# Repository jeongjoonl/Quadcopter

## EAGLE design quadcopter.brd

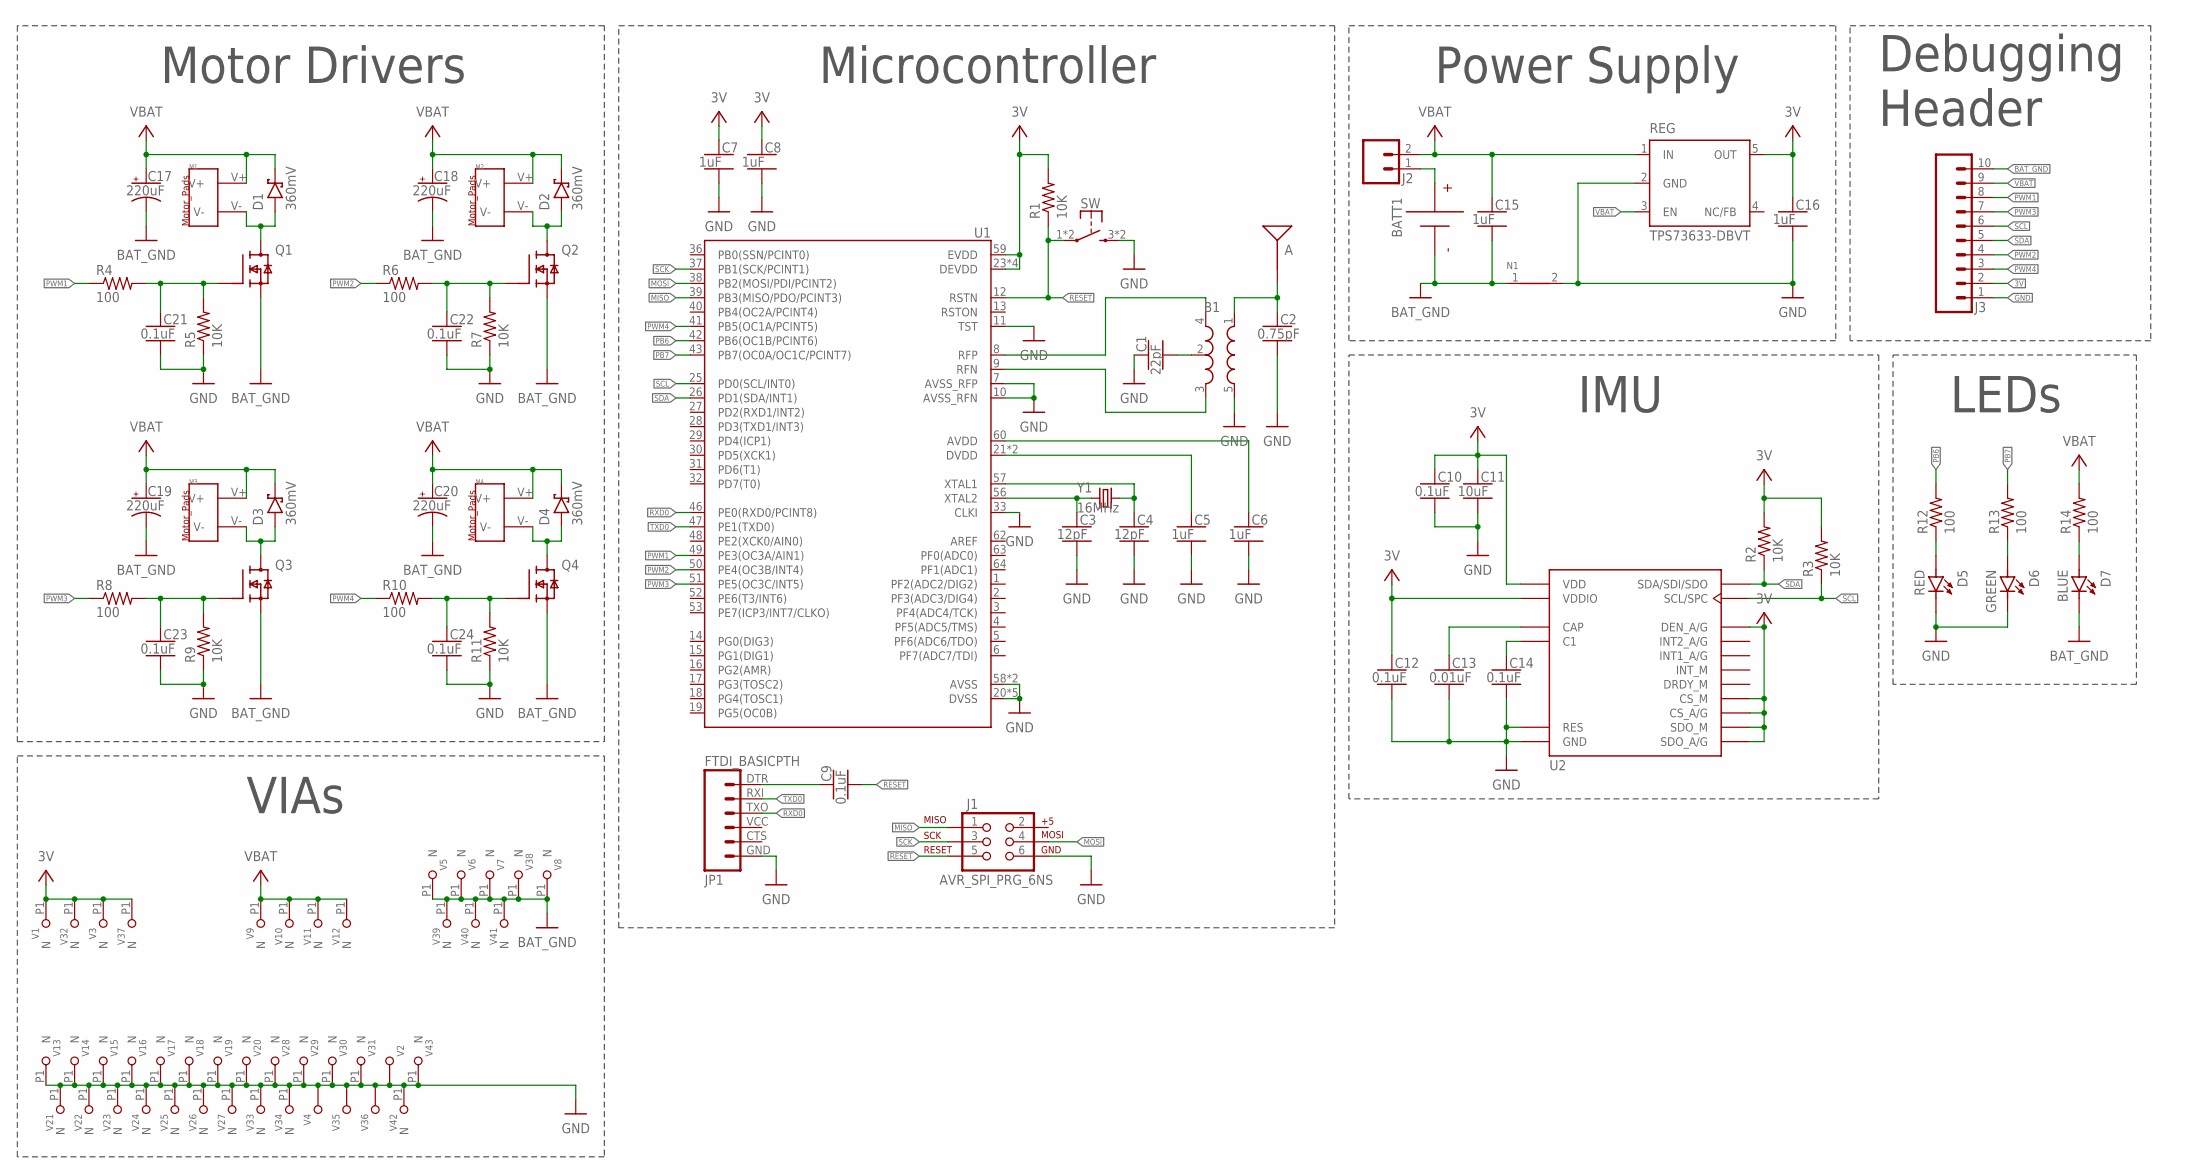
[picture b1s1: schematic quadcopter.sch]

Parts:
A: ANTENNA2SMD5; ANTENNA-CHIP5
B1: BALUN0805; BALUN
BATT1: BATTERY; BATTERY-TERMINALS
C1: 22pF; CAPC2012X140_HS
C2: 0.75pF; CAPC2012X140_HS
C3, C4: 12pF; CAPC2012X140_HS
C5, C6, C7, C8, C15, C16: 1uF; CAPC2012X140_HS
C9, C10, C12, C14, C21, C22, C23, C24: 0.1uF; CAPC2012X140_HS
C11: 10uF; CAPC2012X140_HS
C13: 0.01uF; CAPC2012X140_HS
C17, C18, C19, C20: 220uF; CAPMP7343X310_HS
D1, D2, D3, D4: 360mV; SOD3716X135_HS
D5: RED; LED_0805
D6: GREEN; LED_0805
D7: BLUE; LED_0805
J1: AVR_SPI_PRG_6NS; 2X3-NS
J2: MALE_HEADER_2POS-2X1-0.1IN; MALE_HEADER_2X1_0.1IN
J3: SIP-10_TH-254X10; HDRV10W63P254_10X1_2540X254H838_HS
JP1: FTDI_BASICPTH; FTDI_BASIC
M1, M2, M3, M4: MOTOR_PADS
N1: NET_BRIDGE
Q1, Q2, Q3, Q4: MOSFET_SOT-23; SI2302CDS_T1_E3
R1, R2, R3, R5, R7, R9, R11: 10K; RESC2012X60_HS
R4, R6, R8, R10, R12, R13, R14: 100; RESC2012X60_HS
REG: TPS73633-DBVT; SOT23-DBV
SW: PUSHBUTTON_SMD-VERTICAL-1; TE_FSM8JSMA_HS
U1: ATMEGA128RFA1; QFN-64
U2: IMU_LSM9DS1TR; LSM9DS1TR
V1, V3, V5, V6, V7, V8, V9, V10, V11, V12, V13, V14, V15, V16, V17, V18, V19, V20, V21, V22, V23, V24, V25, V26, V27, V28, V29, V30, V31, V32, V33, V34, V37, V38, V39, V40, V41, V42, V43: LOCKED-VIA-0.254; VIA-0.254MM
V2, V4, V35, V36: VIA_0.454
Y1: 16MHz; CRYSTAL-SMD-5X3

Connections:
3V: C7.1, C8.1, C10.1, C11.1, C12.1, C16.1, J3.2, R1.2, R2.2, R3.2, REG.5 (OUT), U1.23 (DEVDD), U1.34 (DEVDD), U1.44 (DEVDD), U1.54 (DEVDD), U1.59 (EVDD), U2.CS_A/G, U2.CS_M, U2.DEN_A/G, U2.SDO_A/G, U2.SDO_M, U2.VDD, U2.VDDIO, U2.VDDIO_3 (VDDIO), U2.VDD_23 (VDD), V1.P1, V3.P1, V32.P1, V37.P1
BATT1: BATT1.+, J2.1
BAT_GND: BATT1.- (N), C15.2, C17.2 (-), C18.2 (-), C19.2 (-), C20.2 (-), D7.C, J3.10, N1.1, Q1.S, Q2.S, Q3.S, Q4.S, V5.P1, V6.P1, V7.P1, V8.P1, V38.P1, V39.P1, V40.P1, V41.P1
C1: B1.2 (GND), C1.2
C2: A.FEED, B1.1 (IN), C2.1
C3: C3.1, U1.56 (XTAL2), Y1.1
C4: C4.1, U1.57 (XTAL1), Y1.3 (2)
C5: C5.1, U1.21 (DVDD), U1.22 (DVDD)
C6: C6.1, U1.60 (AVDD)
C9: C9.1, JP1.DTR (1)
C13: C13.1, U2.CAP
C14: C14.1, U2.C1
C21: C21.1, Q1.G, R4.2, R5.2
C22: C22.1, Q2.G, R6.2, R7.2
C23: C23.1, Q3.G, R8.2, R9.2
C24: C24.1, Q4.G, R10.2, R11.2
D5: D5.A, R12.1
D6: D6.A, R13.1
D7: D7.A, R14.1
GND: B1.5 (GND), C1.1, C2.2, C3.2, C4.2, C5.2, C6.2, C7.2, C8.2, C10.2, C11.2, C12.2, C13.2, C14.2, C16.2, C21.2, C22.2, C23.2, C24.2, D5.C, D6.C, J1.6, J3.1, JP1.GND (6), N1.2, R5.1, R7.1, R9.1, R11.1, REG.2 (GND), SW.3 (2), SW.4 (2), U1.7 (AVSS_RFP), U1.10 (AVSS_RFN), U1.11 (TST), U1.20 (DVSS), U1.24 (DVSS), U1.33 (CLKI), U1.35 (DVSS), U1.45 (DVSS), U1.55 (DVSS), U1.58 (AVSS), U1.61 (AVSS), U2.GND, U2.GND_20 (GND), U2.RES, U2.RES_15 (RES), U2.RES_16 (RES), U2.RES_17 (RES), U2.RES_18 (RES), V2.VIA, V4.VIA, V13.P1, V14.P1, V15.P1, V16.P1, V17.P1, V18.P1, V19.P1, V20.P1, V21.P1, V22.P1, V23.P1, V24.P1, V25.P1, V26.P1, V27.P1, V28.P1, V29.P1, V30.P1, V31.P1, V33.P1, V34.P1, V35.VIA, V36.VIA, V42.P1, V43.P1
M1: D1.A, M1.V-, Q1.D
M2: D2.A, M2.V-, Q2.D
M3: D3.A, M3.V-, Q3.D
M4: D4.A, M4.V-, Q4.D
MISO: J1.1, U1.39 (PB3(MISO/PDO/PCINT3))
MOSI: J1.4, U1.38 (PB2(MOSI/PDI/PCINT2))
PB6: R12.2, U1.42 (PB6(OC1B/PCINT6))
PB7: R13.2, U1.43 (PB7(OC0A/OC1C/PCINT7))
PWM1: J3.8, R4.1, U1.49 (PE3(OC3A/AIN1))
PWM2: J3.4, R6.1, U1.50 (PE4(OC3B/INT4))
PWM3: J3.7, R8.1, U1.51 (PE5(OC3C/INT5))
PWM4: J3.3, R10.1, U1.41 (PB5(OC1A/PCINT5))
RESET: C9.2, J1.5, R1.1, SW.1, SW.2 (1), U1.12 (RSTN)
RFN: B1.3 (OUT2), U1.9 (RFN)
RFP: B1.4 (OUT1), U1.8 (RFP)
RXD0: JP1.TXO (3), U1.46 (PE0(RXD0/PCINT8))
SCK: J1.3, U1.37 (PB1(SCK/PCINT1))
SCL: J3.6, R3.1, U1.25 (PD0(SCL/INT0)), U2.SCL/SPC
SDA: J3.5, R2.1, U1.26 (PD1(SDA/INT1)), U2.SDA/SDI/SDO
TXD0: JP1.RXI (2), U1.47 (PE1(TXD0))
VBAT: C15.1, C17.1 (+), C18.1 (+), C19.1 (+), C20.1 (+), D1.C, D2.C, D3.C, D4.C, J2.2, J3.9, M1.V+, M2.V+, M3.V+, M4.V+, R14.2, REG.1 (IN), REG.3 (EN), V9.P1, V10.P1, V11.P1, V12.P1

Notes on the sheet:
Motor Drivers
IMU
Microcontroller
Power Supply
Debugging Header
LEDs
VIAs

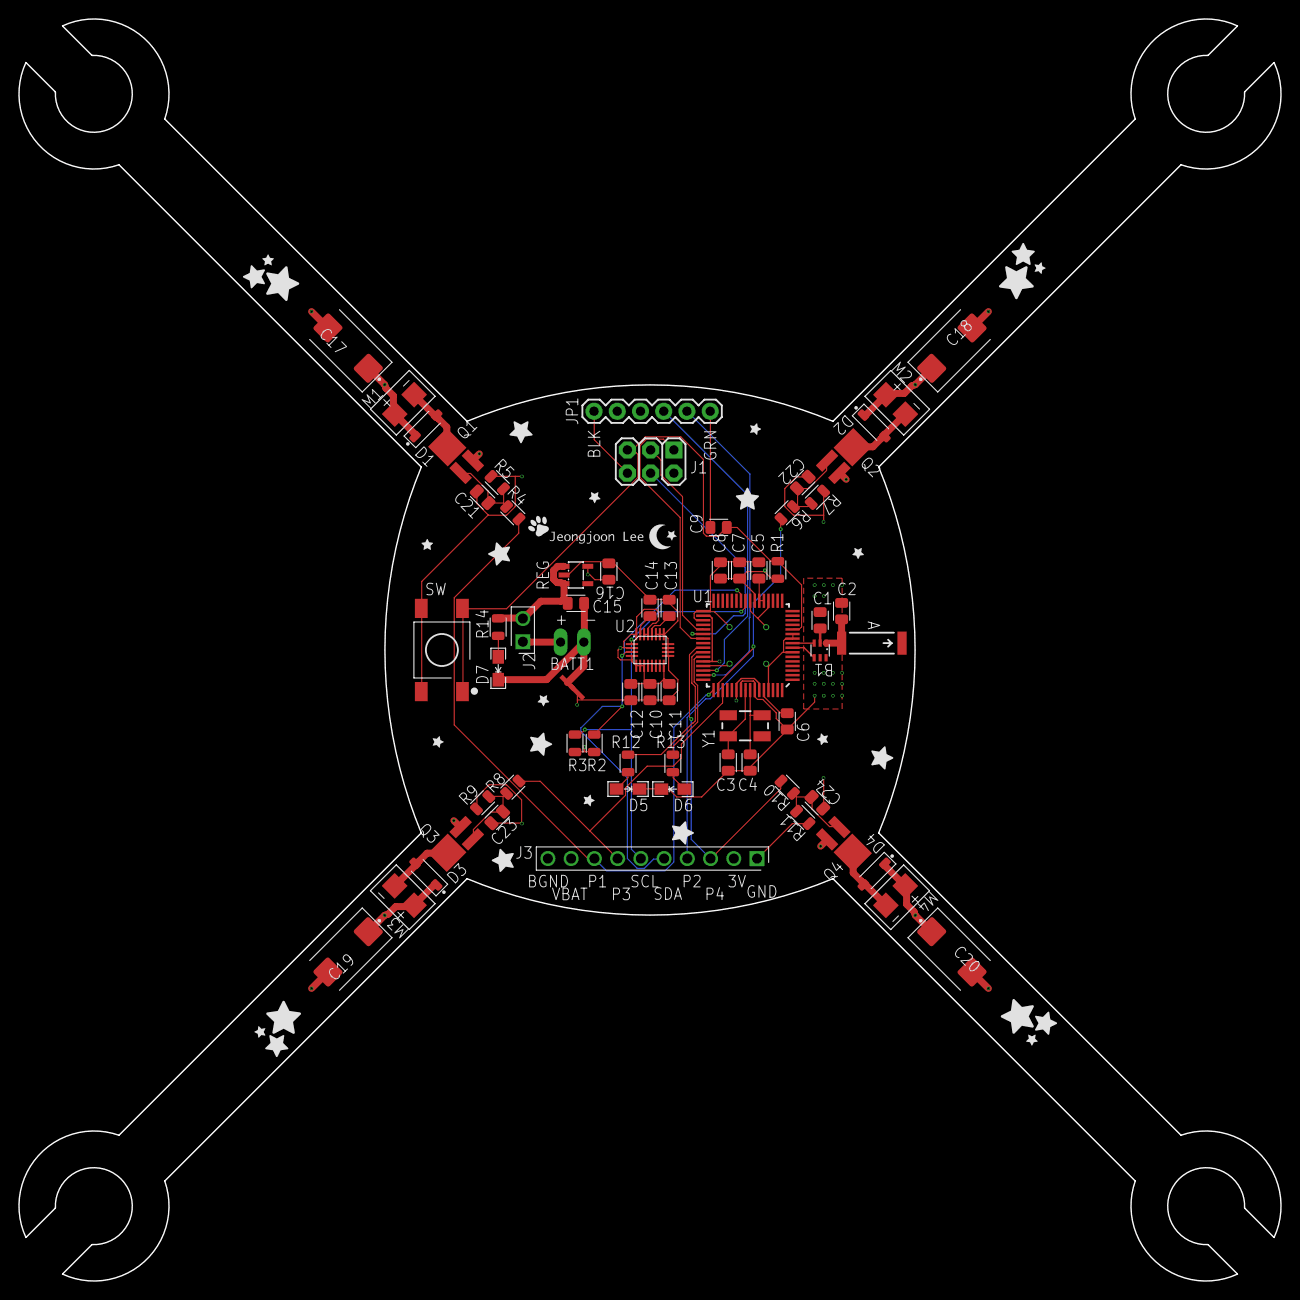
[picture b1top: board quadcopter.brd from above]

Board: 4 copper layers, 138.0 x 138.0 mm, 138 parts (0 on the bottom side), 41 nets.

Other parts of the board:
LOGO1: LOGO_SCALE_0.9_L21
LOGO2: LOGO_SCALE_2.0_L22
STAR1, STAR4, STAR7, STAR10, STAR13, STAR14, STAR15, STAR16, STAR17, STAR18, STAR19, STAR20: STAR_SCALE_0.1_L21
STAR2, STAR5, STAR8, STAR11, STAR21, STAR22, STAR23, STAR24, STAR25, STAR26, STAR27: STAR_SCALE_0.2_L21
STAR3, STAR6, STAR9, STAR12: STAR_SCALE_0.3_L21

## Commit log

2018-04-28 Added Readme.md
2018-04-29 Added datasheets, prebuilt lib and Motor schem
2018-04-30 Add custom lib
2018-04-30 Added quadcopter schem
2018-05-03 Added LED library
2018-05-05 Update custom library
2018-05-05 Removed quad schem
2018-05-05 Testing eagle version
2018-05-06 Added cam and dru files
2018-05-06 Modified LEDs; Add R, G, B leds
2018-05-06 Quadcopter schematic done
2018-05-06 Dimension complete
2018-05-07 Rename N0 net
2018-05-07 Redesign board dimension
2018-05-07 Placed some parts on the board
2018-05-07 Board design continue
2018-05-08 Finished board design
2018-05-08 Changed net bridge
2018-05-08 Modified board design
2018-05-08 Added tPlace for debugger header
2018-05-08 Added more messurement
2018-05-08 Cam file
2018-05-08 Update prebuilt lib
2018-05-08 Update board and schem according to prebuilt lib
2018-05-09 New cam file
2018-05-09 Added logo
2018-05-09 Add logo lib
2018-05-09 Add 1.0mm via
2018-05-09 Added logo on board
2018-05-09 Changed via device
2018-05-09 Redesigned board
2018-05-09 Changed width of high current and add orphans prop
2018-05-09 Cam update
2018-05-09 Orphans did not applied. Now it is
2018-05-09 Added more scale for logo
2018-05-09 Redesigned board and reduced vias
2018-05-09 Minor change
2018-05-10 Added scaled 2.0 layer 22 logo
2018-05-10 Fixed router under antenna driver
2018-05-10 Logo layer 22 fixed
2018-05-10 Added extra resources
2018-05-10 Added pcb top/bottom design
2018-05-10 Added schematic picture
2018-05-10 Update my name
2018-05-10 Added more pcb color
2018-05-10 Fixed logo name
2018-05-10 Added star silkscreen package
2018-05-10 Shink motors components and modified pours
2018-05-10 Added star image
2018-05-10 Changed scale
2018-05-10 Finalized version v0.5.0
2018-05-10 Prev cam file did not work
2018-05-10 Modified screenshots
2018-05-10 Shrink antenna driver pour
2018-05-11 Add another GND pour on layer 15 for antenna driver
2018-05-11 Added 2 more vias around antenna driver
2018-05-19 fixed bPlace logo
2018-05-20 Added soldering list
